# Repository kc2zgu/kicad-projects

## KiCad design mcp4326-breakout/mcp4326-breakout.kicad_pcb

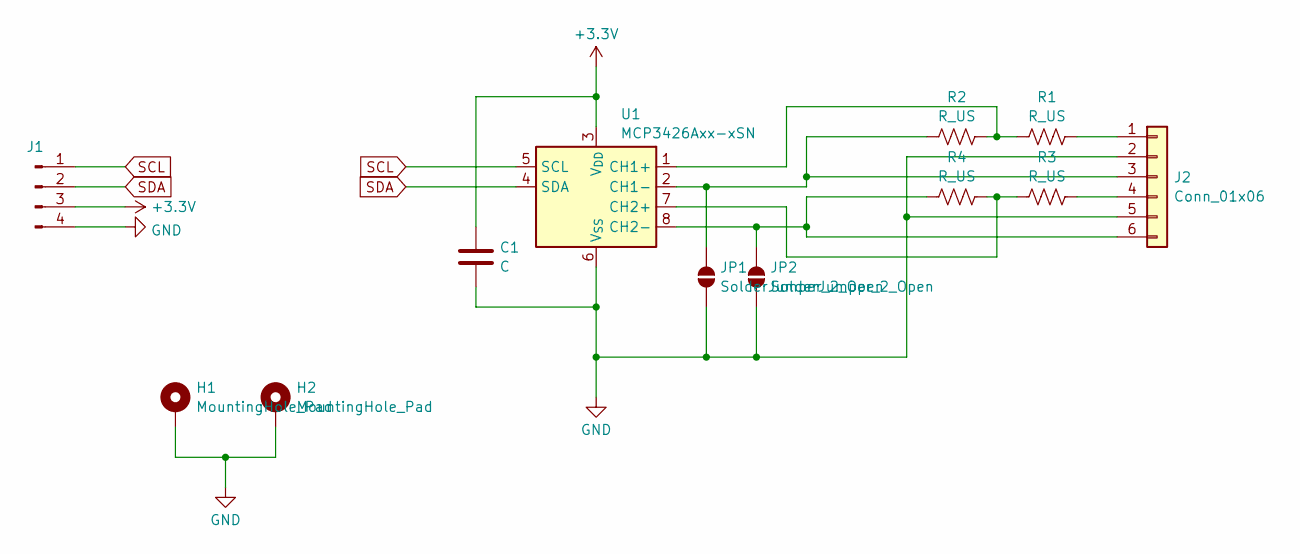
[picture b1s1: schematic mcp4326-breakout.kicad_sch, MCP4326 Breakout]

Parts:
C1: C; C_1210_3225Metric_Pad1.33x2.70mm_HandSolder
H1, H2: MountingHole_Pad; MountingHole_3.2mm_M3_Pad
J1: Conn_01x04_Male; JST_PH_B4B-PH-K_1x04_P2.00mm_Vertical
J2: Conn_01x06; TerminalBlock_TE_282834-6_1x06_P2.54mm_Horizontal
JP1, JP2: SolderJumper_2_Open; SolderJumper-2_P1.3mm_Open_RoundedPad1.0x1.5mm
R1, R2, R3, R4: R_US; R_0805_2012Metric_Pad1.20x1.40mm_HandSolder
U1: MCP3426Axx-xSN; SOIC-8_3.9x4.9mm_P1.27mm

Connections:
+3.3V: C1.1, J1.3, U1.3 (V_{DD})
GND: C1.2, H1.1, H2.1, J1.4, J2.2, J2.5, JP1.1 (A), JP2.1 (A), U1.6 (V_{SS})
unnamed: J2.1, R1.2
unnamed: J2.3, JP1.2 (B), R2.1, U1.2 (CH1-)
unnamed: J2.4, R3.2
unnamed: J2.6, JP2.2 (B), R4.1, U1.8 (CH2-)
unnamed: R1.1, R2.2, U1.1 (CH1+)
unnamed: R3.1, R4.2, U1.7 (CH2+)
SCL: J1.1, U1.5 (SCL)
SDA: J1.2, U1.4 (SDA)

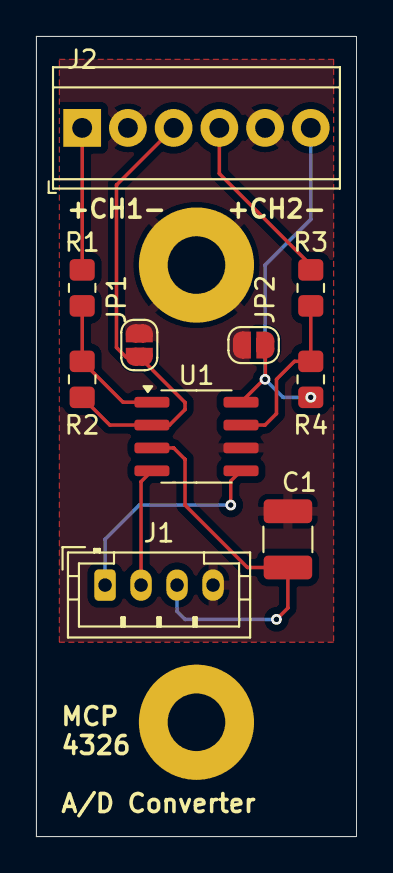
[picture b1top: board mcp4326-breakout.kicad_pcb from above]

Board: 2 copper layers, 17.8 x 44.5 mm, 12 parts (0 on the bottom side), 10 nets.

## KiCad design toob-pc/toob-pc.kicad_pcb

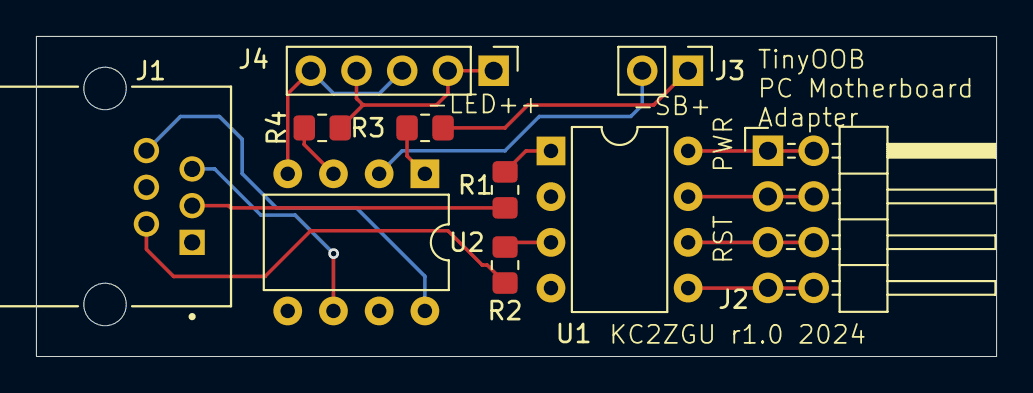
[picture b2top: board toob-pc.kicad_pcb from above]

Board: 2 copper layers, 53.3 x 17.8 mm, 10 parts (0 on the bottom side), 17 nets.

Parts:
J1: 6P6C; CUI_CRJ030-G-TH
J2: Conn_02x04_Odd_Even; PinHeader_2x04_P2.54mm_Horizontal
J3: Conn_01x02_Pin; PinHeader_1x02_P2.54mm_Vertical
J4: Conn_01x05_Pin; PinHeader_1x05_P2.54mm_Vertical
R1, R2, R3, R4: R_US; R_0805_2012Metric_Pad1.20x1.40mm_HandSolder
U1, U2: PC827; DIP-8_W7.62mm

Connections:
/PSW: J2.1, J2.2, U1.8
/PSWG: J2.3, J2.4, U1.7
/RSW: J2.5, J2.6, U1.6
/RSWG: J2.7, J2.8, U1.5
GND: J1.1, J1.4, U1.2, U1.4, U2.5, U2.7
unnamed: J1.2, R2.1
unnamed: J1.3, R1.1
unnamed: J1.5, U2.6
unnamed: J1.6, U2.8
unnamed: J3.1, R3.2
unnamed: J3.2, U2.2
unnamed: J4.1, J4.2, J4.4, R4.2
unnamed: J4.3, J4.5, U2.4
unnamed: R1.2, U1.1
unnamed: R2.2, U1.3
unnamed: R3.1, U2.1
unnamed: R4.1, U2.3

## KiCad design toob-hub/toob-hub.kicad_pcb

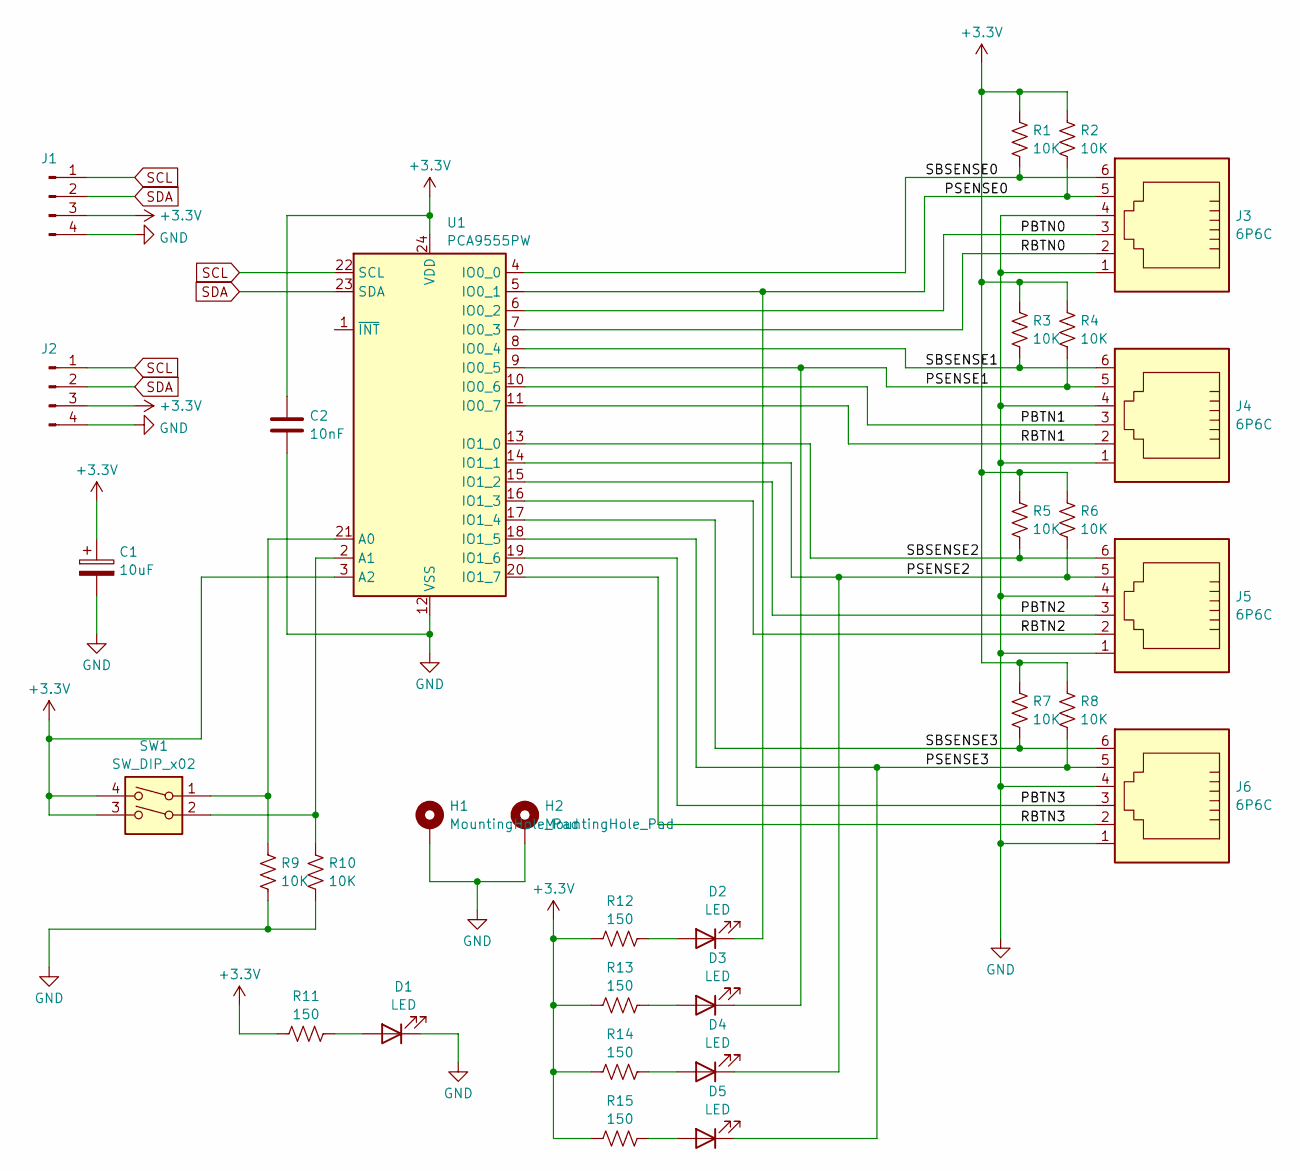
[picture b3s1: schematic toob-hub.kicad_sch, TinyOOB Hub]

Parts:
C1: 10uF; CP_Radial_D5.0mm_P2.50mm
C2: 10nF; C_0805_2012Metric_Pad1.18x1.45mm_HandSolder
D1, D2, D3, D4, D5: LED; LED_D3.0mm
H1, H2: MountingHole_Pad; MountingHole_3.2mm_M3_DIN965_Pad
J1, J2: Conn_01x04_Male; JST_PH_B4B-PH-K_1x04_P2.00mm_Vertical
J3, J4, J5, J6: 6P6C; CUI_CRJ030-G-TH
R1, R2, R3, R4, R5, R6, R7, R8, R9, R10: 10K; R_0805_2012Metric_Pad1.20x1.40mm_HandSolder
R11, R12, R13, R14, R15: 150; R_0805_2012Metric_Pad1.20x1.40mm_HandSolder
SW1: SW_DIP_x02; SW_DIP_SPSTx02_Slide_6.7x6.64mm_W7.62mm_P2.54mm_LowProfile
U1: PCA9555PW; TSSOP-24_4.4x7.8mm_P0.65mm

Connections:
+3.3V: C1.1, C2.1, J1.3, J2.3, R1.1, R2.1, R3.1, R4.1, R5.1, R6.1, R7.1, R8.1, R11.1, R12.1, R13.1, R14.1, R15.1, SW1.3, SW1.4, U1.3 (A2), U1.24 (VDD)
/PBTN0: J3.3, U1.6 (IO0_2)
/PBTN1: J4.3, U1.10 (IO0_6)
/PBTN2: J5.3, U1.15 (IO1_2)
/PBTN3: J6.3, U1.19 (IO1_6)
/PSENSE0: D2.1 (K), J3.5, R2.2, U1.5 (IO0_1)
/PSENSE1: D3.1 (K), J4.5, R4.2, U1.9 (IO0_5)
/PSENSE2: D4.1 (K), J5.5, R6.2, U1.14 (IO1_1)
/PSENSE3: D5.1 (K), J6.5, R8.2, U1.18 (IO1_5)
/RBTN0: J3.2, U1.7 (IO0_3)
/RBTN1: J4.2, U1.11 (IO0_7)
/RBTN2: J5.2, U1.16 (IO1_3)
/RBTN3: J6.2, U1.20 (IO1_7)
/SBSENSE0: J3.6, R1.2, U1.4 (IO0_0)
/SBSENSE1: J4.6, R3.2, U1.8 (IO0_4)
/SBSENSE2: J5.6, R5.2, U1.13 (IO1_0)
/SBSENSE3: J6.6, R7.2, U1.17 (IO1_4)
GND: C1.2, C2.2, D1.1 (K), H1.1, H2.1, J1.4, J2.4, J3.1, J3.4, J4.1, J4.4, J5.1, J5.4, J6.1, J6.4, R9.2, R10.2, U1.12 (VSS)
unnamed: D1.2 (A), R11.2
unnamed: D2.2 (A), R12.2
unnamed: D3.2 (A), R13.2
unnamed: D4.2 (A), R14.2
unnamed: D5.2 (A), R15.2
unnamed: R9.1, SW1.1, U1.21 (A0)
unnamed: R10.1, SW1.2, U1.2 (A1)
SCL: J1.1, J2.1, U1.22 (SCL)
SDA: J1.2, J2.2, U1.23 (SDA)

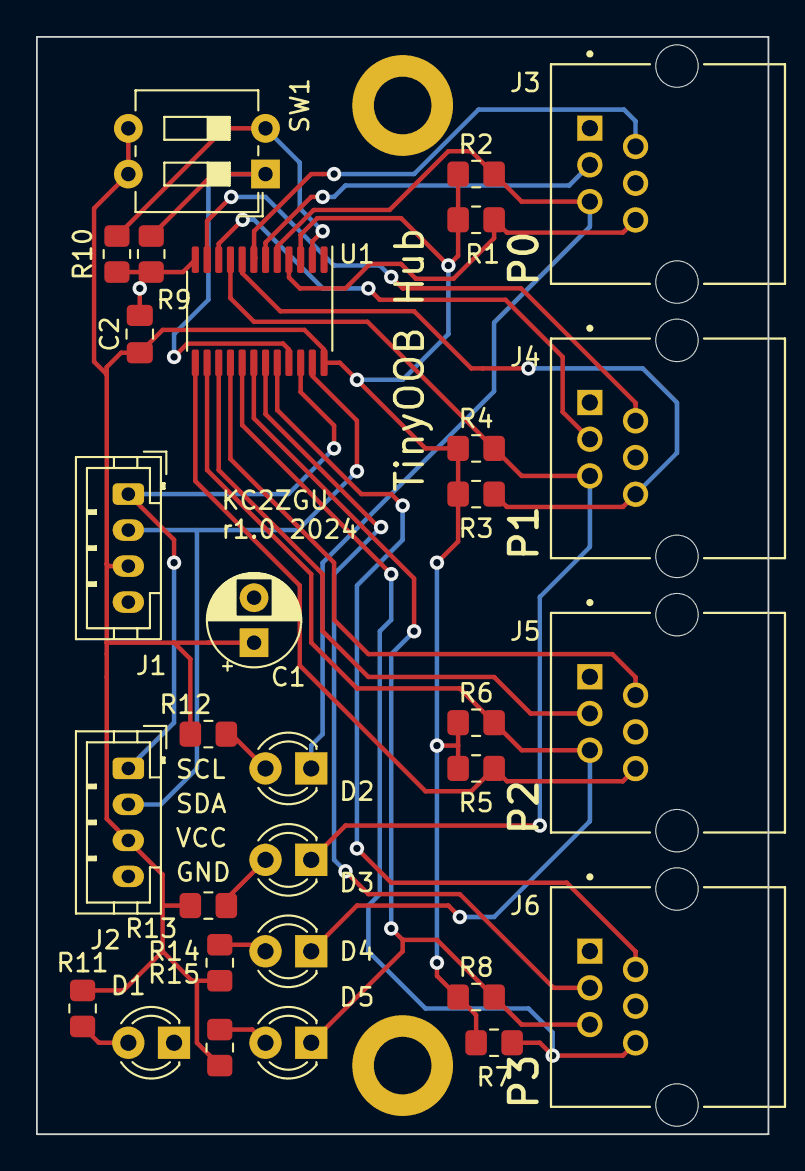
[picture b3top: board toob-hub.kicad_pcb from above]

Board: 2 copper layers, 40.6 x 61.0 mm, 32 parts (0 on the bottom side), 27 nets.

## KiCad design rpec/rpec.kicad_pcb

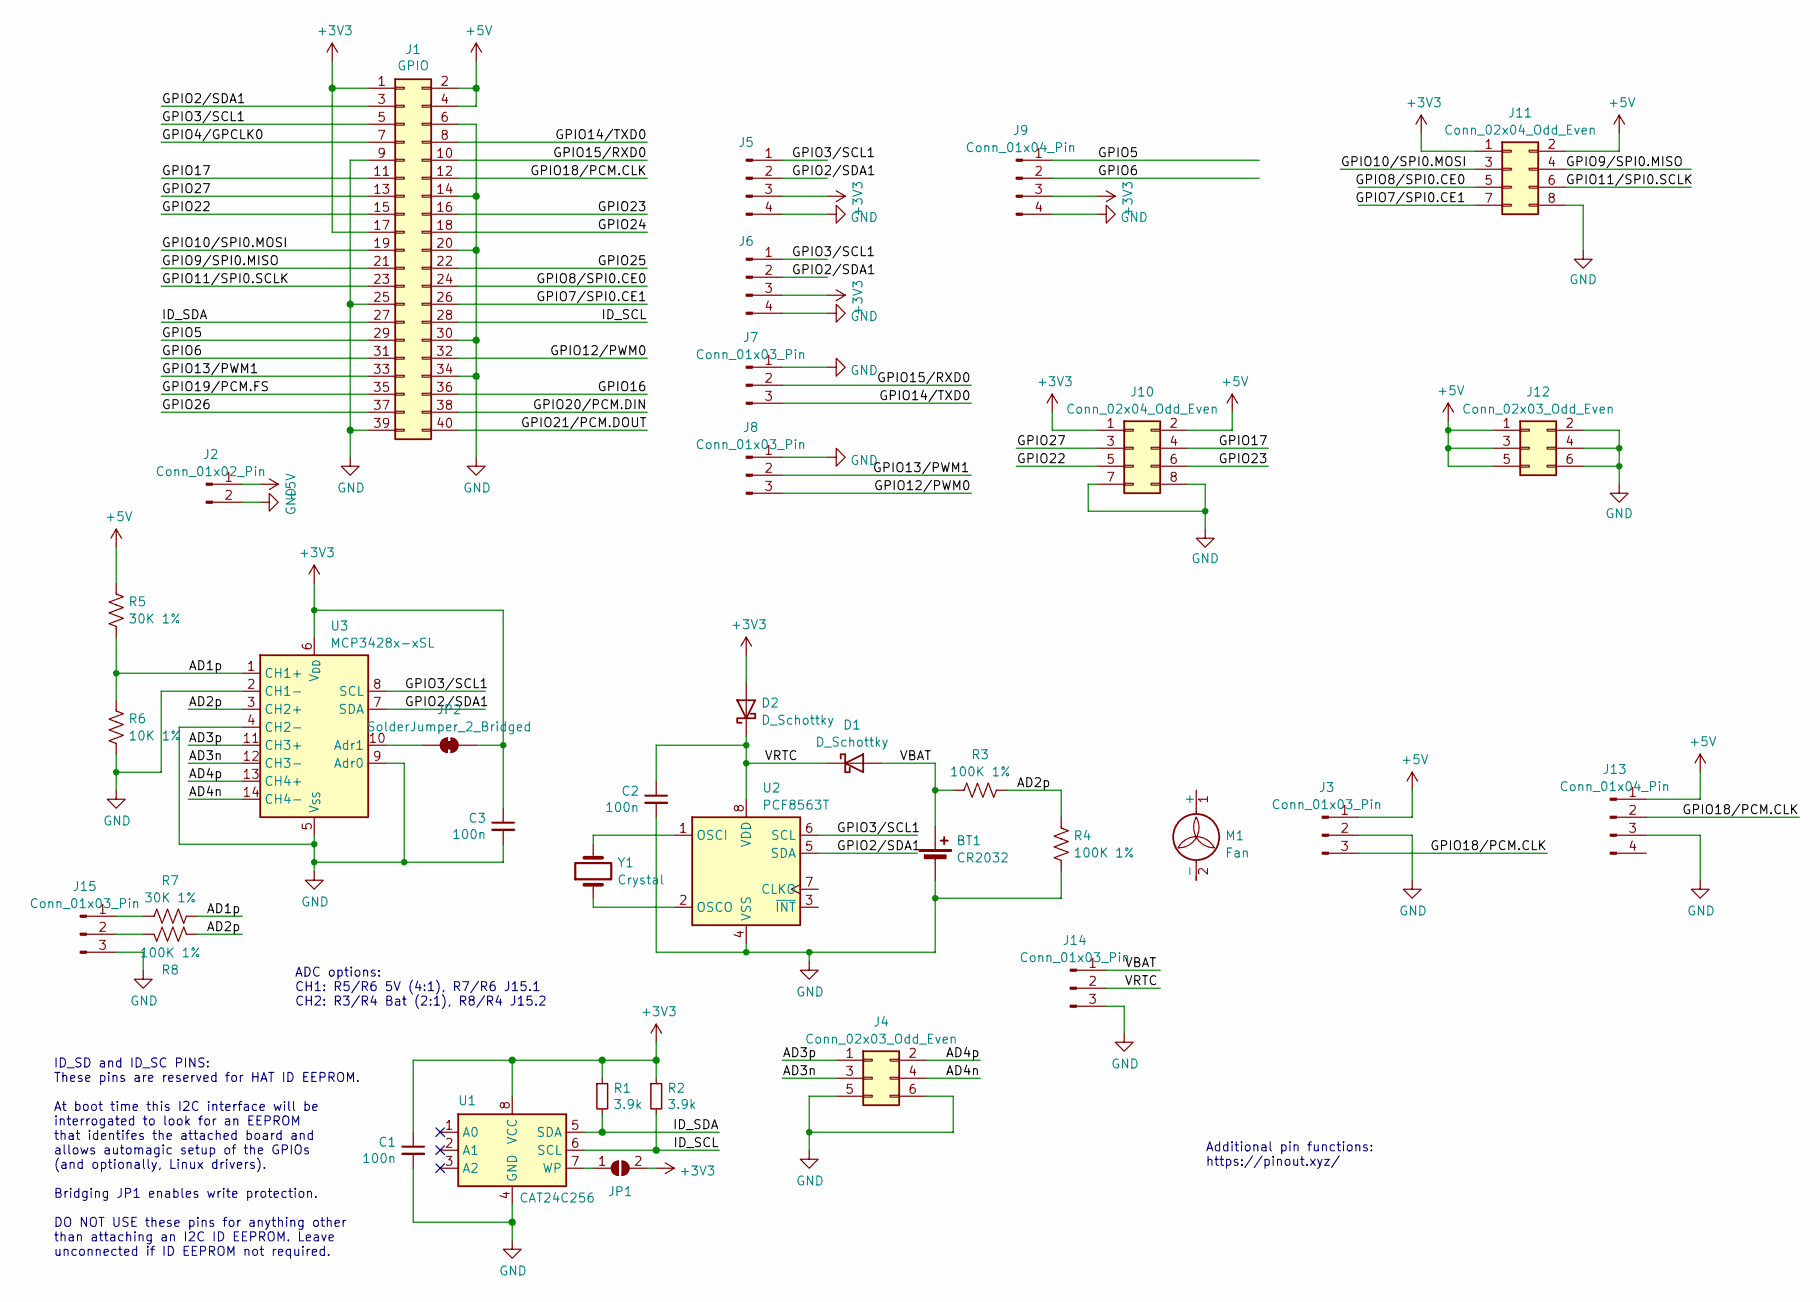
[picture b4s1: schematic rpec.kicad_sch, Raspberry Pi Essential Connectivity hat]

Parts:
BT1: CR2032; BatteryHolder_MPD_BC2003_1x2032
C1, C2, C3: 100n; C_0805_2012Metric_Pad1.18x1.45mm_HandSolder
D1, D2: D_Schottky; D_MiniMELF
J1: GPIO; PinSocket_2x20_P2.54mm_Vertical
J2: Conn_01x02_Pin; JST_PH_B2B-PH-K_1x02_P2.00mm_Vertical
J3: Conn_01x03_Pin; JST_ZH_B3B-ZR_1x03_P1.50mm_Vertical
J4, J12: Conn_02x03_Odd_Even; PinHeader_2x03_P2.54mm_Vertical
J5, J6: Conn_01x04_Male; JST_PH_B4B-PH-K_1x04_P2.00mm_Vertical
J7, J8, J15: Conn_01x03_Pin; PinHeader_1x03_P2.54mm_Vertical
J9: Conn_01x04_Pin; PinHeader_1x04_P2.54mm_Vertical
J10, J11: Conn_02x04_Odd_Even; PinHeader_2x04_P2.54mm_Vertical
J13: Conn_01x04_Pin; JST_SH_BM04B-SRSS-TB_1x04-1MP_P1.00mm_Vertical
J14: Conn_01x03_Pin; JST_PH_B3B-PH-K_1x03_P2.00mm_Vertical
JP1: ID_WP; SolderJumper-2_P1.3mm_Open_RoundedPad1.0x1.5mm
JP2: SolderJumper_2_Bridged; SolderJumper-2_P1.3mm_Bridged_RoundedPad1.0x1.5mm
M1: Fan; Fan_30mm
R1, R2: 3.9k; R_0805_2012Metric_Pad1.20x1.40mm_HandSolder
R3, R4, R8: 100K 1%; R_0805_2012Metric_Pad1.20x1.40mm_HandSolder
R5, R7: 30K 1%; R_0805_2012Metric_Pad1.20x1.40mm_HandSolder
R6: 10K 1%; R_0805_2012Metric_Pad1.20x1.40mm_HandSolder
U1: CAT24C256; SOIC-8_3.9x4.9mm_P1.27mm
U2: PCF8563T; SOIC-8_3.9x4.9mm_P1.27mm
U3: MCP3428x-xSL; SOIC-14_3.9x8.7mm_P1.27mm
Y1: Crystal; Crystal_SMD_3215-2Pin_3.2x1.5mm

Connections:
+3V3: C1.1, C3.1, D2.2 (A), J1.1, J1.17, J5.3, J6.3, J9.3, J10.1, J11.1, JP1.2 (B), JP2.2 (B), R1.1, R2.1, U1.8 (VCC), U3.6 (V_{DD})
+5V: J1.2, J1.4, J2.1, J3.1, J10.2, J11.2, J12.1, J12.3, J12.5, J13.1, R5.2
/AD1p: R5.1, R6.2, R7.1, U3.1 (CH1+)
/AD2p: R3.2, R4.2, R8.1, U3.3 (CH2+)
/AD3n: J4.3, U3.12 (CH3-)
/AD3p: J4.1, U3.11 (CH3+)
/AD4n: J4.4, U3.14 (CH4-)
/AD4p: J4.2, U3.13 (CH4+)
/GPIO2/SDA1: J1.3, J5.2, J6.2, U2.5 (SDA), U3.7 (SDA)
/GPIO3/SCL1: J1.5, J5.1, J6.1, U2.6 (SCL), U3.8 (SCL)
/GPIO4/GPCLK0: J1.7
/GPIO5: J1.29, J9.1
/GPIO6: J1.31, J9.2
/GPIO7/SPI0.CE1: J1.26, J11.7
/GPIO8/SPI0.CE0: J1.24, J11.5
/GPIO9/SPI0.MISO: J1.21, J11.4
/GPIO10/SPI0.MOSI: J1.19, J11.3
/GPIO11/SPI0.SCLK: J1.23, J11.6
/GPIO12/PWM0: J1.32, J8.3
/GPIO13/PWM1: J1.33, J8.2
/GPIO14/TXD0: J1.8, J7.3
/GPIO15/RXD0: J1.10, J7.2
/GPIO16: J1.36
/GPIO17: J1.11, J10.4
/GPIO18/PCM.CLK: J1.12, J3.3, J13.2
/GPIO19/PCM.FS: J1.35
/GPIO20/PCM.DIN: J1.38
/GPIO21/PCM.DOUT: J1.40
/GPIO22: J1.15, J10.5
/GPIO23: J1.16, J10.6
/GPIO24: J1.18
/GPIO25: J1.22
/GPIO26: J1.37
/GPIO27: J1.13, J10.3
/ID_SCL: J1.28, R2.2, U1.6 (SCL)
/ID_SDA: J1.27, R1.2, U1.5 (SDA)
/VBAT: BT1.1 (+), D1.2 (A), J14.1, R3.1
/VRTC: C2.1, D1.1 (K), D2.1 (K), J14.2, U2.8 (VDD)
GND: BT1.2 (-), C1.2, C2.2, C3.2, J1.6, J1.9, J1.14, J1.20, J1.25, J1.30, J1.34, J1.39, J2.2, J3.2, J4.5, J4.6, J5.4, J6.4, J7.1, J8.1, J9.4, J10.7, J10.8, J11.8, J12.2, J12.4, J12.6, J13.3, J14.3, J15.3, R4.1, R6.1, U1.4 (GND), U2.4 (VSS), U3.2 (CH1-), U3.4 (CH2-), U3.5 (V_{SS}), U3.9 (Adr0)
unnamed: J15.1, R7.2
unnamed: J15.2, R8.2
unnamed: JP1.1 (A), U1.7 (WP)
unnamed: JP2.1 (A), U3.10 (Adr1)
unnamed: U2.1 (OSCI), Y1.2
unnamed: U2.2 (OSCO), Y1.1

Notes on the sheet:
Additional pin functions: https://pinout.xyz/
ID_SD and ID_SC PINS: These pins are reserved for HAT ID EEPROM. At boot time this I2C interface will be interrogated to look for an EEPROM that identifes the attached board and allows automagic setup of the GPIOs (and optionally, Linux drivers). Bridging JP1 enables write protection. DO NOT USE th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
ADC options: CH1: R5/R6 5V (4:1), R7/R6 J15.1 CH2: R3/R4 Bat (2:1), R8/R4 J15.2

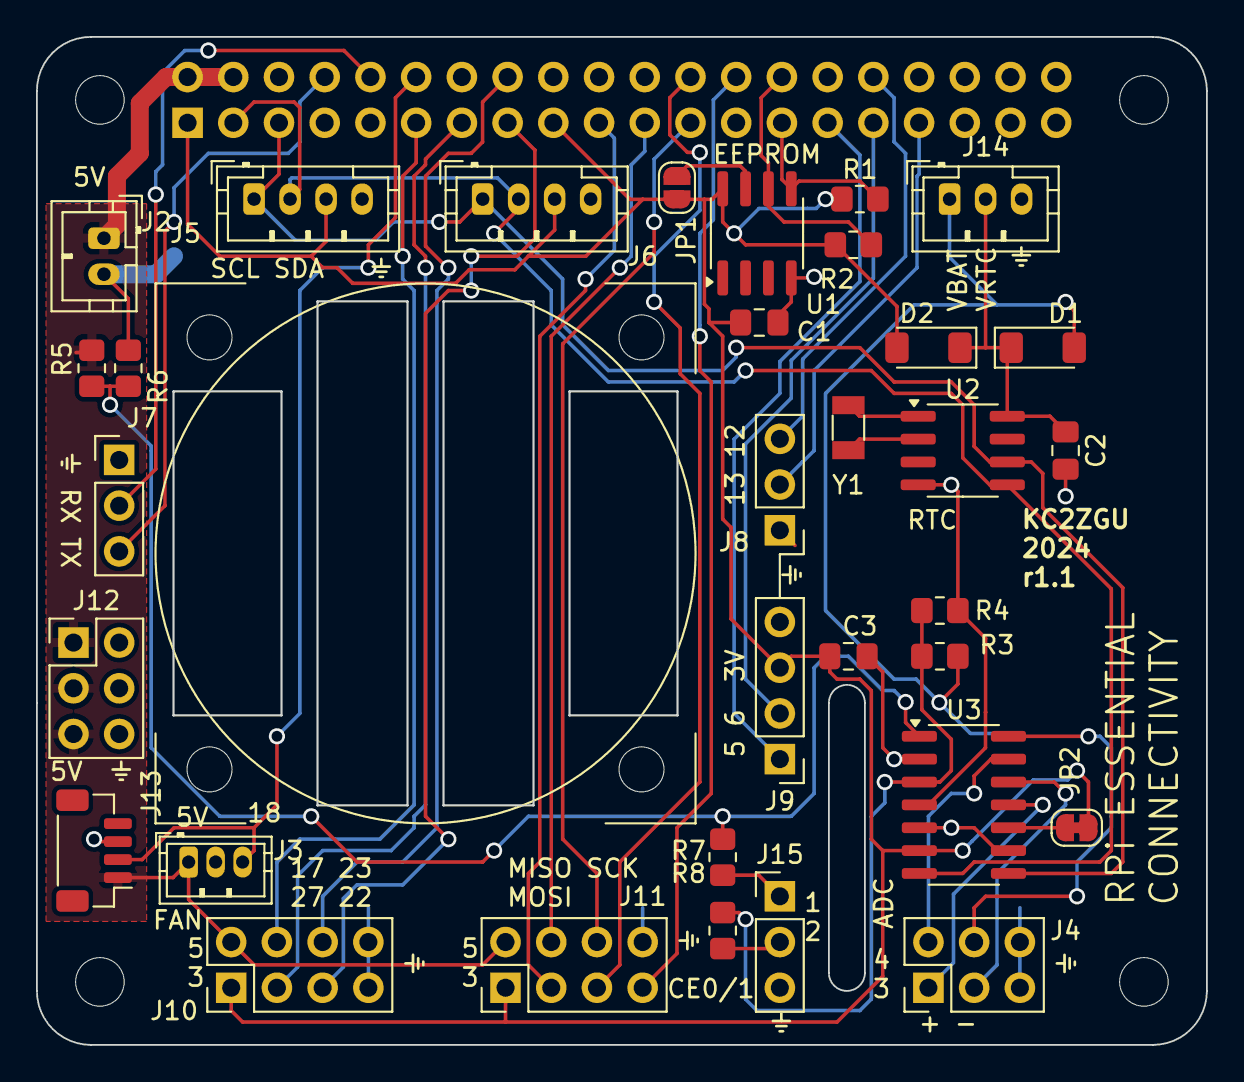
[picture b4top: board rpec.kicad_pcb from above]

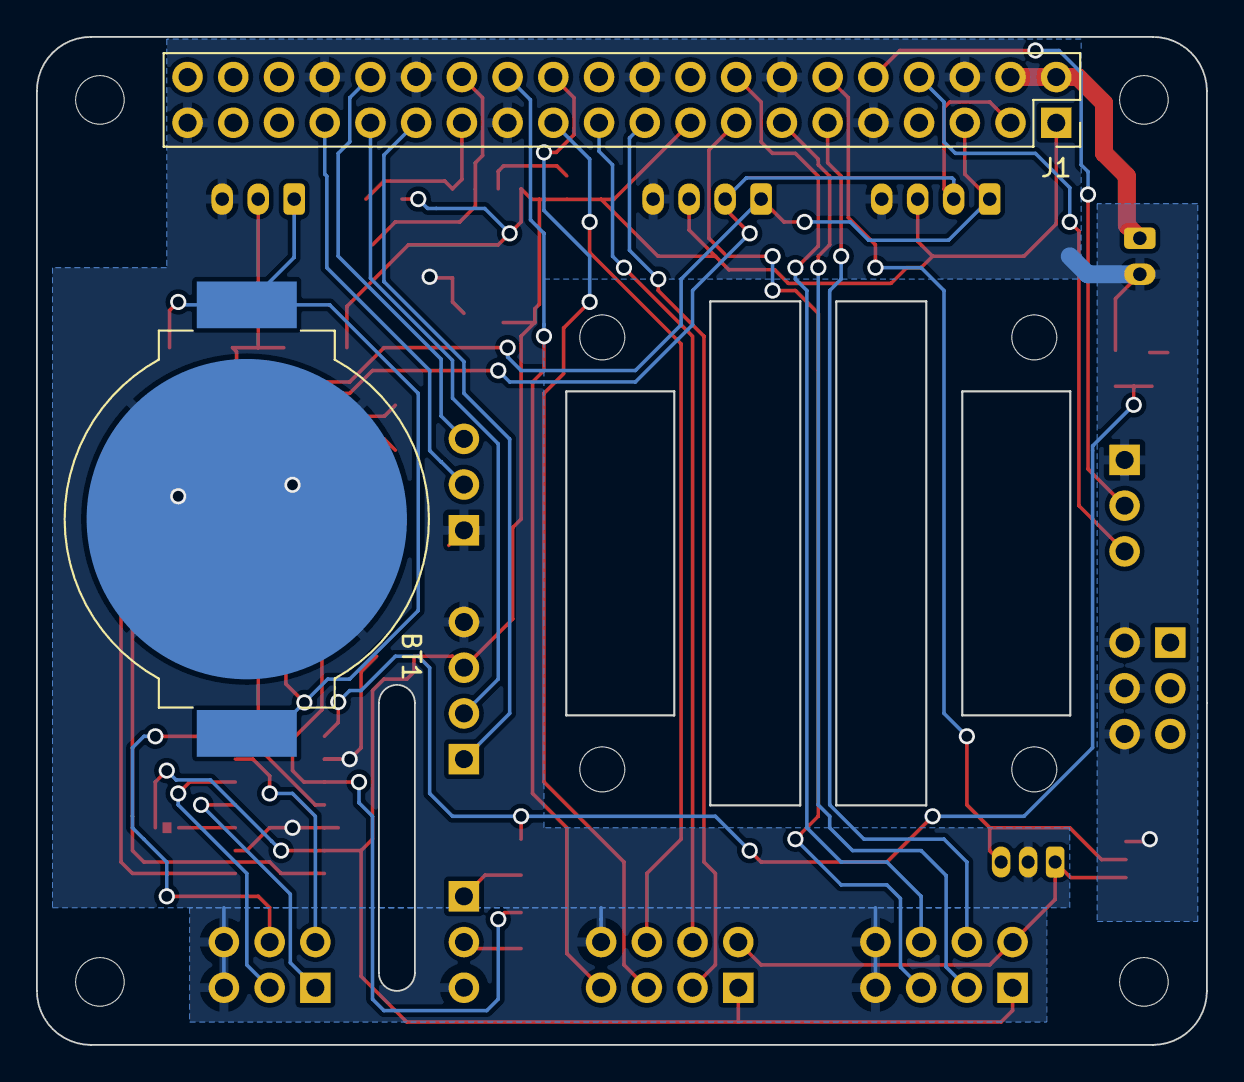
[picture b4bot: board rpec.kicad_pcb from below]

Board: 2 copper layers, 65.0 x 56.0 mm, 40 parts (2 on the bottom side), 37 nets.

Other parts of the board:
MH1, MH2, MH3, MH4: MountingHole_2.7mm_M2.5

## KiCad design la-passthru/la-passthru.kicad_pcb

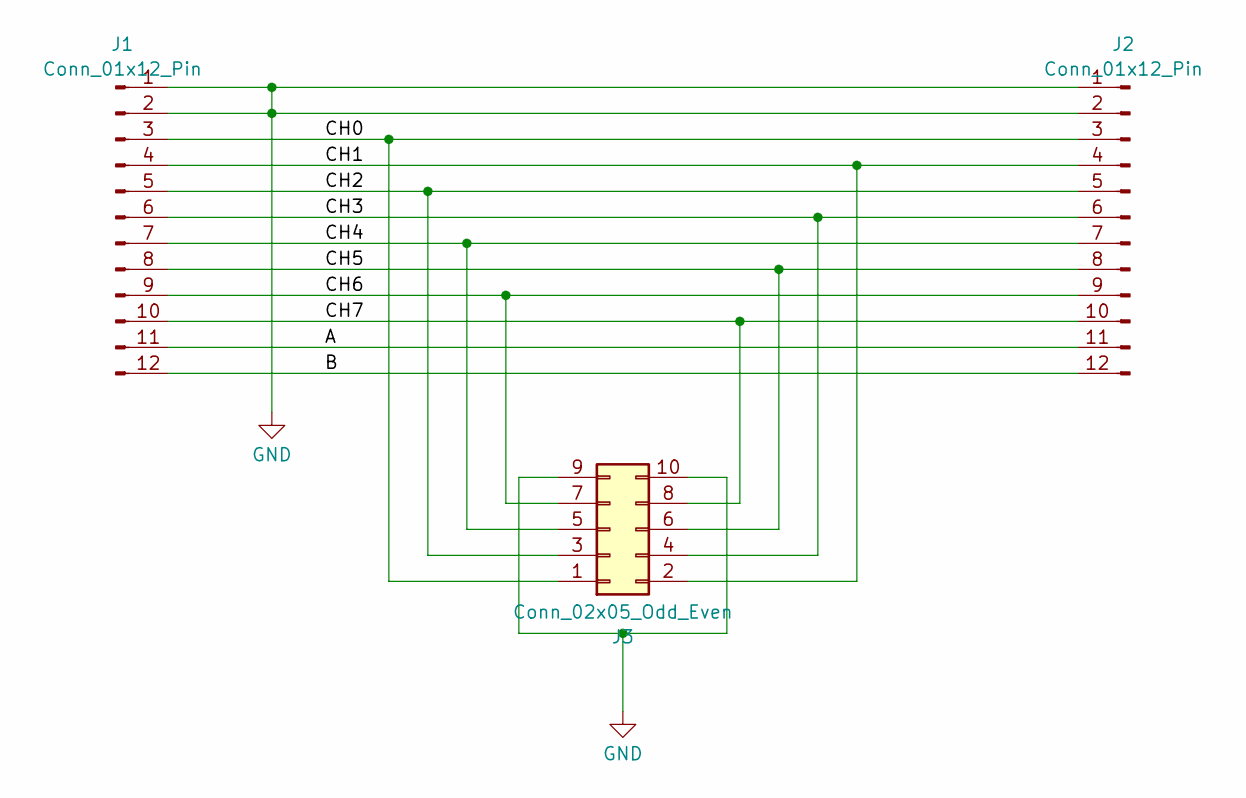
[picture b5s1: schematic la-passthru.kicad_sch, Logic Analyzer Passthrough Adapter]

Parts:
J1, J2: Conn_01x12_Pin; PinHeader_1x12_P2.54mm_Vertical
J3: Conn_02x05_Odd_Even; PinSocket_2x05_P2.54mm_Horizontal

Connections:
/A: J1.11, J2.11
/B: J1.12, J2.12
/CH0: J1.3, J2.3, J3.1
/CH1: J1.4, J2.4, J3.2
/CH2: J1.5, J2.5, J3.3
/CH3: J1.6, J2.6, J3.4
/CH4: J1.7, J2.7, J3.5
/CH5: J1.8, J2.8, J3.6
/CH6: J1.9, J2.9, J3.7
/CH7: J1.10, J2.10, J3.8
GND: J1.1, J1.2, J2.1, J2.2, J3.9, J3.10

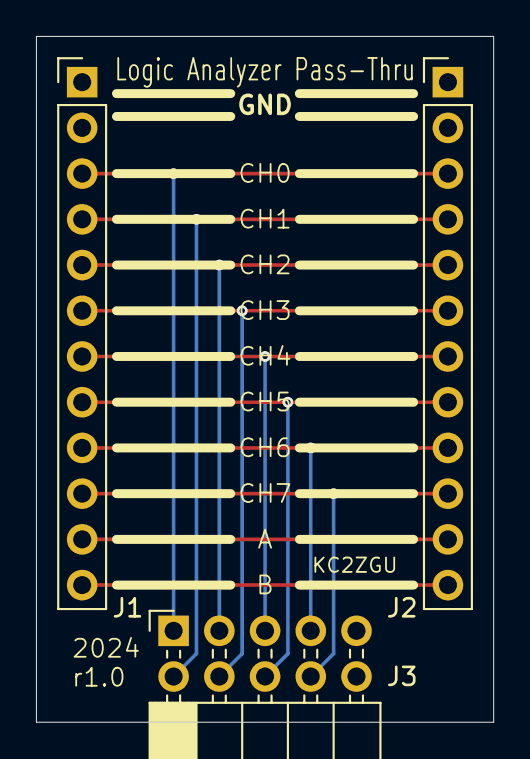
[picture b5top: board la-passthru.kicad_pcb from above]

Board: 2 copper layers, 25.4 x 38.1 mm, 3 parts (0 on the bottom side), 11 nets.

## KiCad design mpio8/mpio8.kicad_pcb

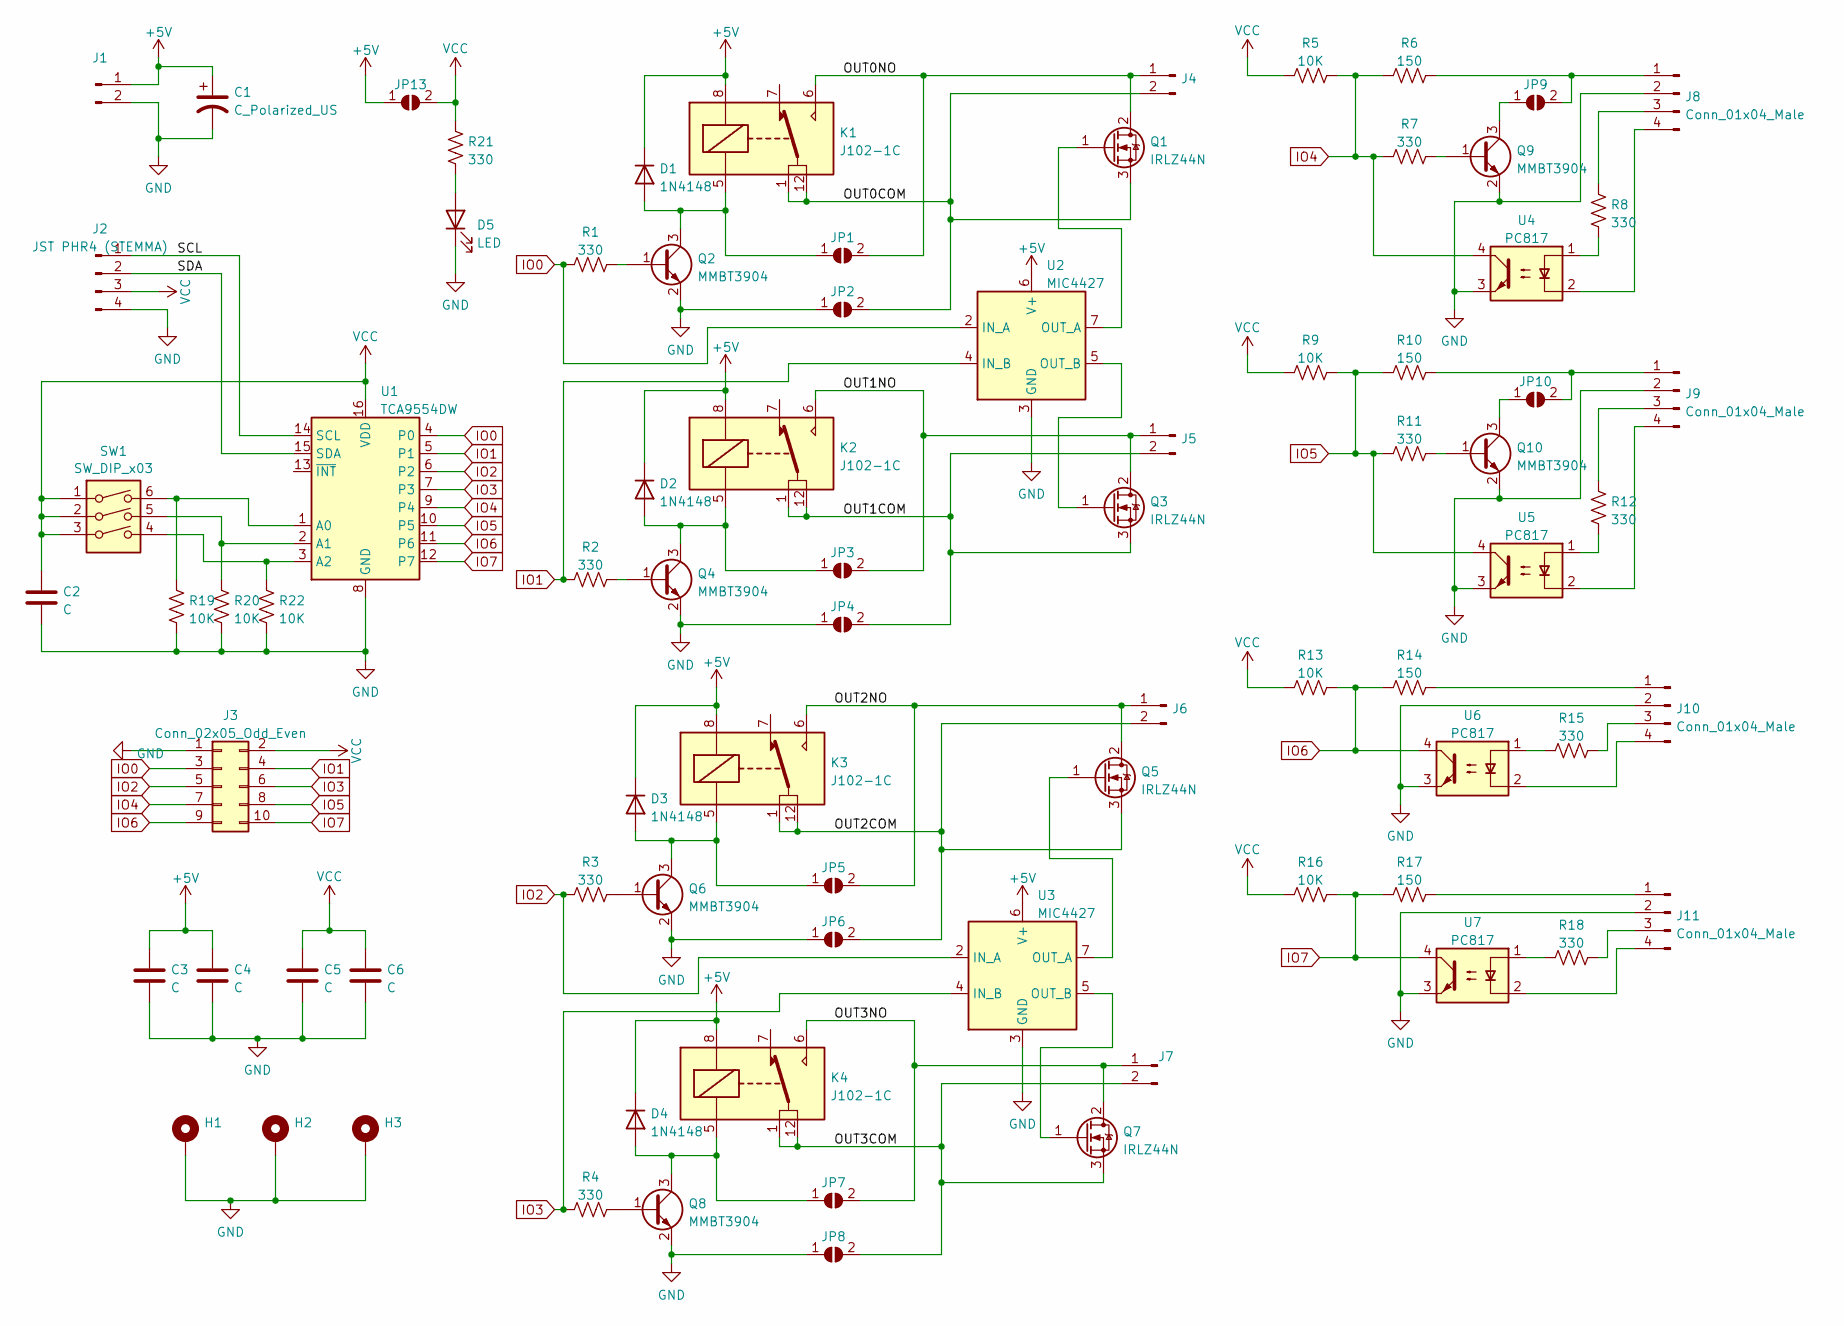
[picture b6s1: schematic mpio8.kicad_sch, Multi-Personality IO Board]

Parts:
C1: C_Polarized_US; CP_Radial_D8.0mm_P2.50mm
C2, C5, C6: C; C_0805_2012Metric
C3, C4: C; C_1206_3216Metric
D1, D2, D3, D4: 1N4148; D_MiniMELF_Handsoldering
D5: LED; LED_D3.0mm
H1, H2, H3: MountingHole_Pad; MountingHole_3.2mm_M3_DIN965_Pad
J1, J4, J5, J6, J7: Conn_01x02_Male; TerminalBlock_bornier-2_P5.08mm
J2: JST PHR4 (STEMMA); JST_PH_B4B-PH-K_1x04_P2.00mm_Vertical
J3: Conn_02x05_Odd_Even; PinHeader_2x05_P2.54mm_Horizontal
J8, J9, J10, J11: Conn_01x04_Male; PinHeader_2x02_P2.54mm_Horizontal
JP1, JP2, JP3, JP4, JP5, JP6, JP7, JP8, JP9, JP10, JP13: SolderJumper_2_Open; SolderJumper-2_P1.3mm_Open_Pad1.0x1.5mm
K1, K2, K3, K4: J102-1C; Relay_SPDT_HJR-4102
Q1, Q3, Q5, Q7: IRLZ44N; TO-220-3_Vertical
Q2, Q4, Q6, Q8, Q9, Q10: MMBT3904; SOT-23
R1, R2, R3, R4, R7, R8, R11, R12, R15, R18, R21: 330; R_0805_2012Metric
R5, R9, R13, R16, R19, R20, R22: 10K; R_0805_2012Metric
R6, R10, R14, R17: 150; R_0805_2012Metric
SW1: SW_DIP_x03; SW_DIP_SPSTx03_Slide_6.7x9.18mm_W7.62mm_P2.54mm_LowProfile
U1: TCA9554DW; SOIC-16W_7.5x10.3mm_P1.27mm
U2, U3: MIC4427; SOIC-8_3.9x4.9mm_P1.27mm
U4, U5, U6, U7: PC817; DIP-4_W7.62mm

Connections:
+5V: C1.1, C3.1, C4.1, D1.1 (K), D2.1 (K), D3.1 (K), D4.1 (K), J1.1, JP13.1 (A), K1.8, K2.8, K3.8, K4.8, U2.6 (V+), U3.6 (V+)
/OUT0COM: J4.2, JP2.2 (B), K1.1, K1.12, Q1.3 (S)
/OUT0NO: J4.1, JP1.2 (B), K1.6, Q1.2 (D)
/OUT1COM: J5.2, JP4.2 (B), K2.1, K2.12, Q3.3 (S)
/OUT1NO: J5.1, JP3.2 (B), K2.6, Q3.2 (D)
/OUT2COM: J6.2, JP6.2 (B), K3.1, K3.12, Q5.3 (S)
/OUT2NO: J6.1, JP5.2 (B), K3.6, Q5.2 (D)
/OUT3COM: J7.2, JP8.2 (B), K4.1, K4.12, Q7.3 (S)
/OUT3NO: J7.1, JP7.2 (B), K4.6, Q7.2 (D)
/SCL: J2.1, U1.14 (SCL)
/SDA: J2.2, U1.15 (SDA)
GND: C1.2, C2.2, C3.2, C4.2, C5.2, C6.2, D5.1 (K), H1.1, H2.1, H3.1, J1.2, J2.4, J3.1, J8.2, J9.2, J10.2, J11.2, JP2.1 (A), JP4.1 (A), JP6.1 (A), JP8.1 (A), Q2.2 (E), Q4.2 (E), Q6.2 (E), Q8.2 (E), Q9.2 (E), Q10.2 (E), R19.1, R20.1, R22.1, U1.8 (GND), U2.3 (GND), U3.3 (GND), U4.3, U5.3, U6.3, U7.3
IO0: J3.3, R1.1, U1.4 (P0), U2.2 (IN_A)
IO1: J3.4, R2.1, U1.5 (P1), U2.4 (IN_B)
IO2: J3.5, R3.1, U1.6 (P2), U3.2 (IN_A)
IO3: J3.6, R4.1, U1.7 (P3), U3.4 (IN_B)
IO4: J3.7, R5.2, R6.1, R7.1, U1.9 (P4), U4.4
IO5: J3.8, R9.2, R10.1, R11.1, U1.10 (P5), U5.4
IO6: J3.9, R13.2, R14.1, U1.11 (P6), U6.4
IO7: J3.10, R16.2, R17.1, U1.12 (P7), U7.4
unnamed: D1.2 (A), JP1.1 (A), K1.5, Q2.3 (C)
unnamed: D2.2 (A), JP3.1 (A), K2.5, Q4.3 (C)
unnamed: D3.2 (A), JP5.1 (A), K3.5, Q6.3 (C)
unnamed: D4.2 (A), JP7.1 (A), K4.5, Q8.3 (C)
unnamed: D5.2 (A), R21.1
unnamed: J8.1, JP9.2 (B), R6.2
unnamed: J8.3, R8.1
unnamed: J8.4, U4.2
unnamed: J9.1, JP10.2 (B), R10.2
unnamed: J9.3, R12.1
unnamed: J9.4, U5.2
unnamed: J10.1, R14.2
unnamed: J10.3, R15.2
unnamed: J10.4, U6.2
unnamed: J11.1, R17.2
unnamed: J11.3, R18.2
unnamed: J11.4, U7.2
unnamed: JP9.1 (A), Q9.3 (C)
unnamed: JP10.1 (A), Q10.3 (C)
unnamed: Q1.1 (G), U2.7 (OUT_A)
unnamed: Q2.1 (B), R1.2
unnamed: Q3.1 (G), U2.5 (OUT_B)
unnamed: Q4.1 (B), R2.2
unnamed: Q5.1 (G), U3.7 (OUT_A)
unnamed: Q6.1 (B), R3.2
unnamed: Q7.1 (G), U3.5 (OUT_B)
unnamed: Q8.1 (B), R4.2
unnamed: Q9.1 (B), R7.2
unnamed: Q10.1 (B), R11.2
unnamed: R8.2, U4.1
unnamed: R12.2, U5.1
unnamed: R15.1, U6.1
unnamed: R18.1, U7.1
unnamed: R19.2, SW1.6, U1.1 (A0)
unnamed: R20.2, SW1.5, U1.2 (A1)
unnamed: R22.2, SW1.4, U1.3 (A2)
VCC: C2.1, C5.1, C6.1, J2.3, J3.2, JP13.2 (B), R5.1, R9.1, R13.1, R16.1, R21.2, SW1.1, SW1.2, SW1.3, U1.16 (VDD)

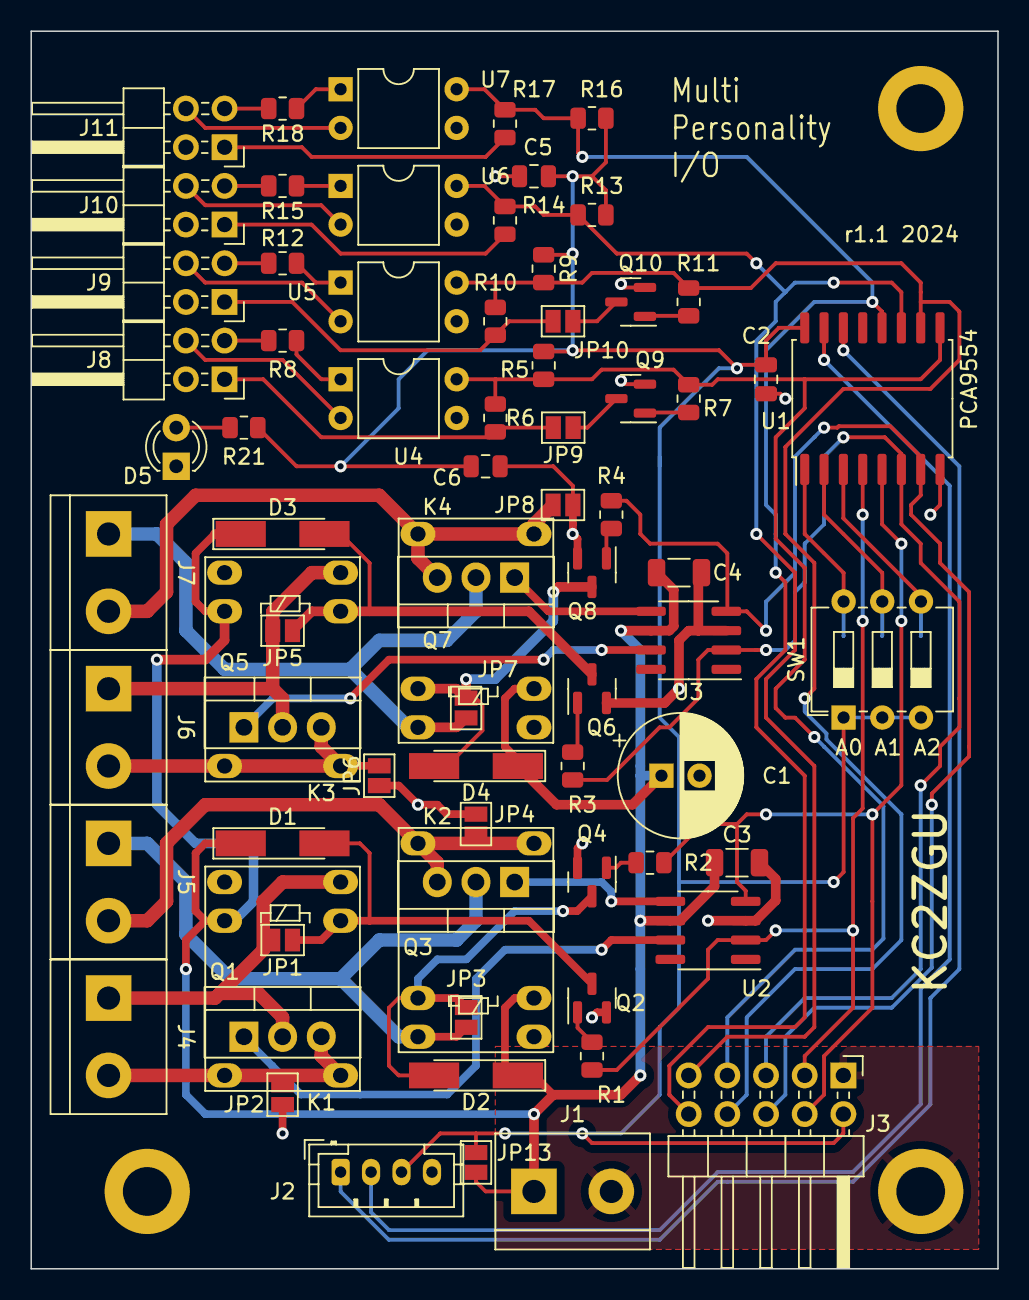
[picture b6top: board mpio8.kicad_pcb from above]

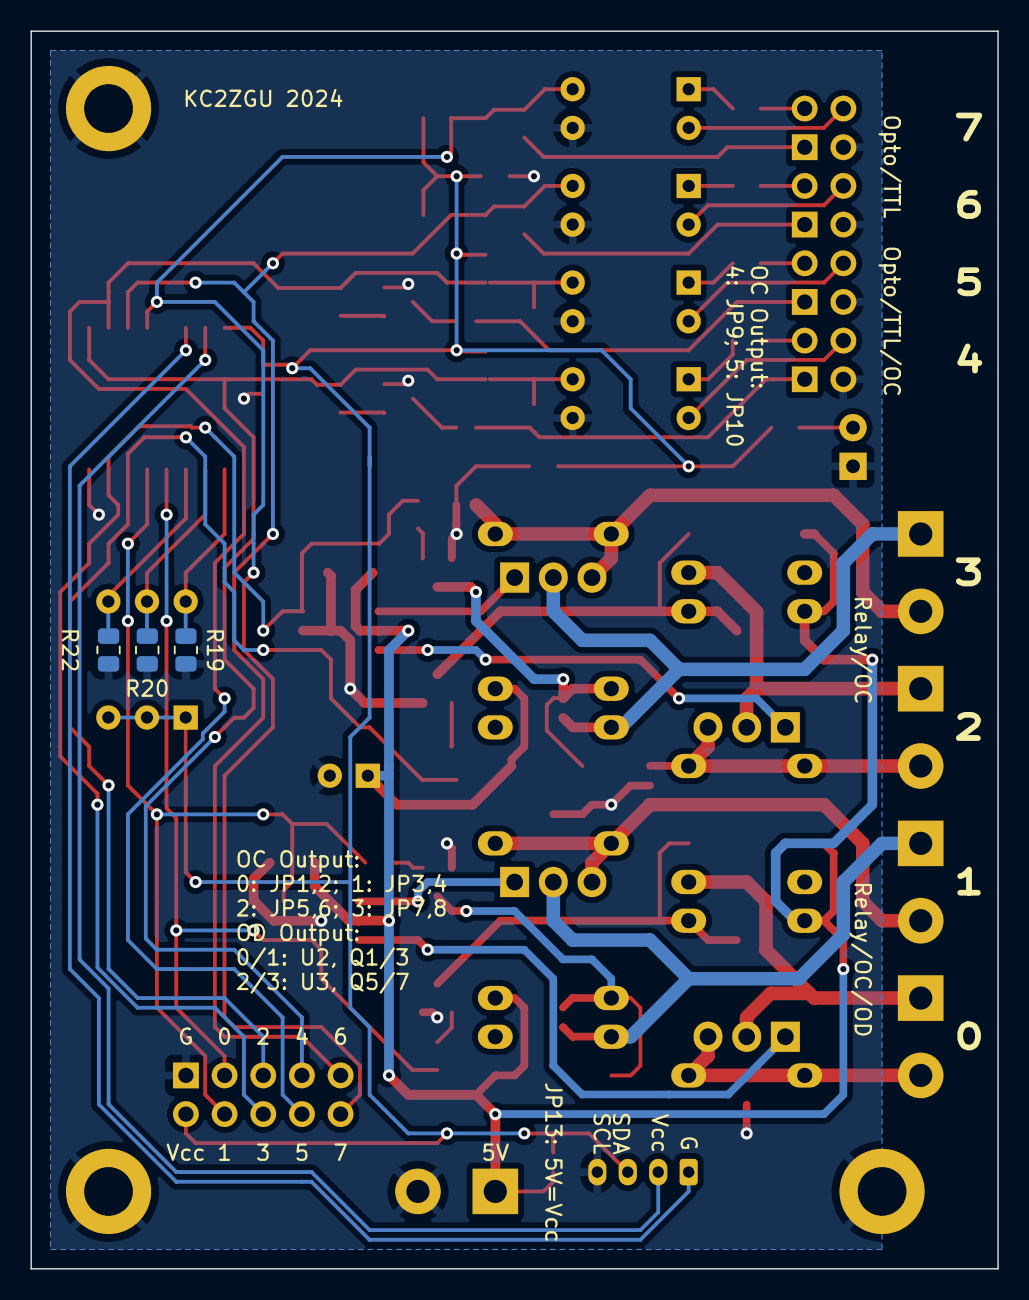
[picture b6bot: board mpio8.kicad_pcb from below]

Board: 2 copper layers, 63.5 x 81.3 mm, 80 parts (3 on the bottom side), 57 nets.

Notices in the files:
rpec/rpec.kicad_sch:
© 2024 Stephen A. Cavilia, CC BY-SA
